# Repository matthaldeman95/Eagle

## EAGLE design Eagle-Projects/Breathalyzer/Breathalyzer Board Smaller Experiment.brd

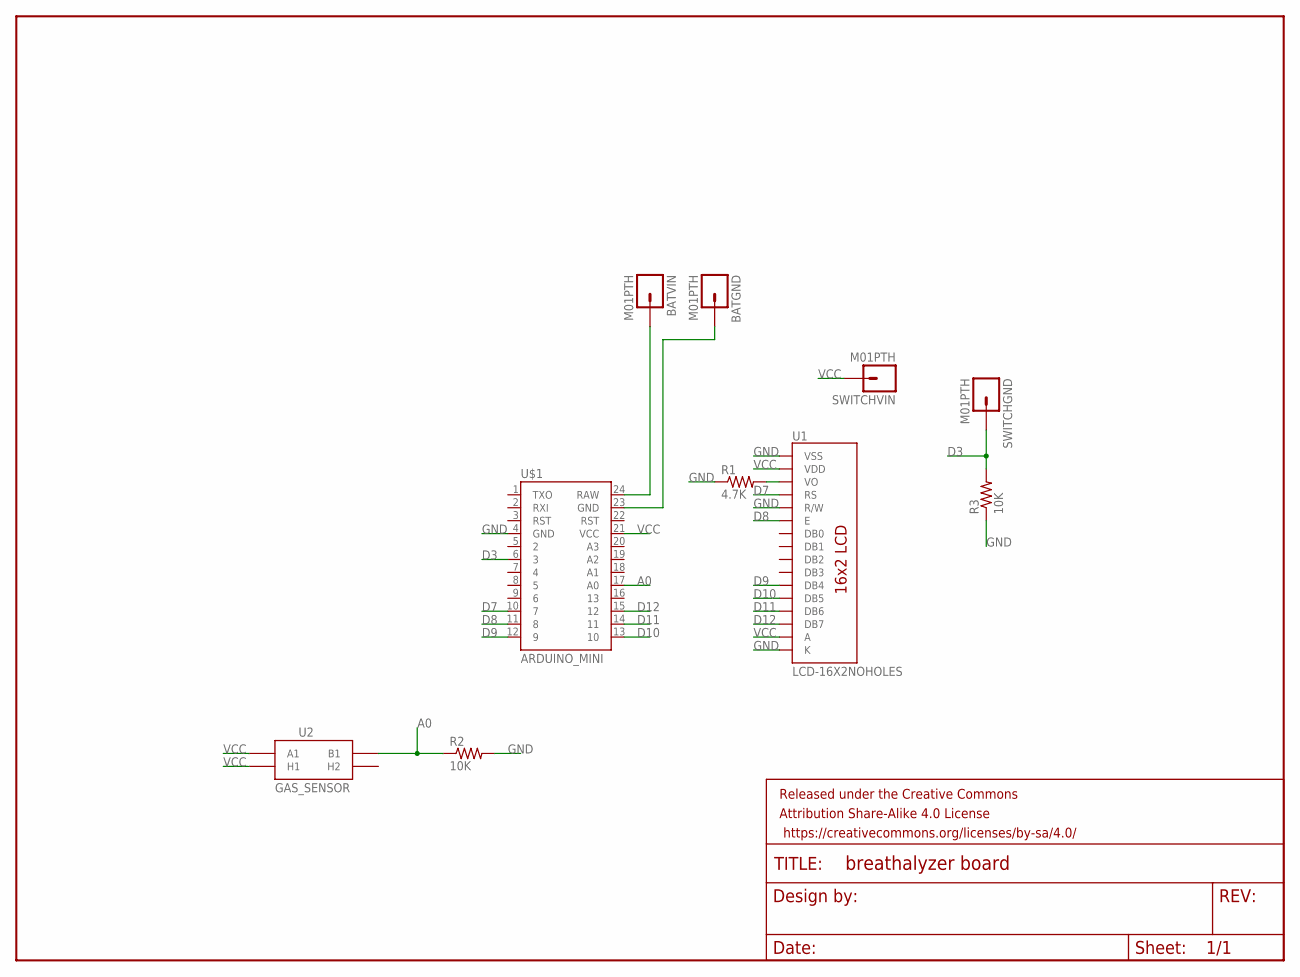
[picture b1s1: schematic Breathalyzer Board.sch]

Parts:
BATGND: M01PTH; 1X01
BATVIN: M01PTH; 1X01
FRAME1: FRAME-LETTER; CREATIVE_COMMONS
R1: 4.7K; AXIAL-0.3
R2, R3: 10K; AXIAL-0.3
SWITCHGND: M01PTH; 1X01
SWITCHVIN: M01PTH; 1X01
U1: LCD-16X2NOHOLES; LCD-16X2_NOHOLES
U2: GAS_SENSOR; MQ-3
U$1: ARDUINO_MINI

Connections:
A0: R2.P$1 (1), U2.B1, U$1.17 (A0)
D3: R3.P$2 (2), SWITCHGND.1, U$1.6 (3)
D7: U1.4 (RS), U$1.10 (7)
D8: U1.6 (E), U$1.11 (8)
D9: U1.11 (DB4), U$1.12 (9)
D10: U1.12 (DB5), U$1.13 (10)
D11: U1.13 (DB6), U$1.14 (11)
D12: U1.14 (DB7), U$1.15 (12)
GND: R1.P$1 (1), R2.P$2 (2), R3.P$1 (1), U1.1 (VSS), U1.5 (R/W), U1.16 (K), U$1.4 (GND)
unnamed: BATVIN.1, U$1.24 (RAW)
unnamed: BATGND.1, U$1.23 (GND)
unnamed: R1.P$2 (2), U1.3 (VO)
VCC: SWITCHVIN.1, U1.2 (VDD), U1.15 (A), U2.A1, U2.HA (H1), U$1.21 (VCC)

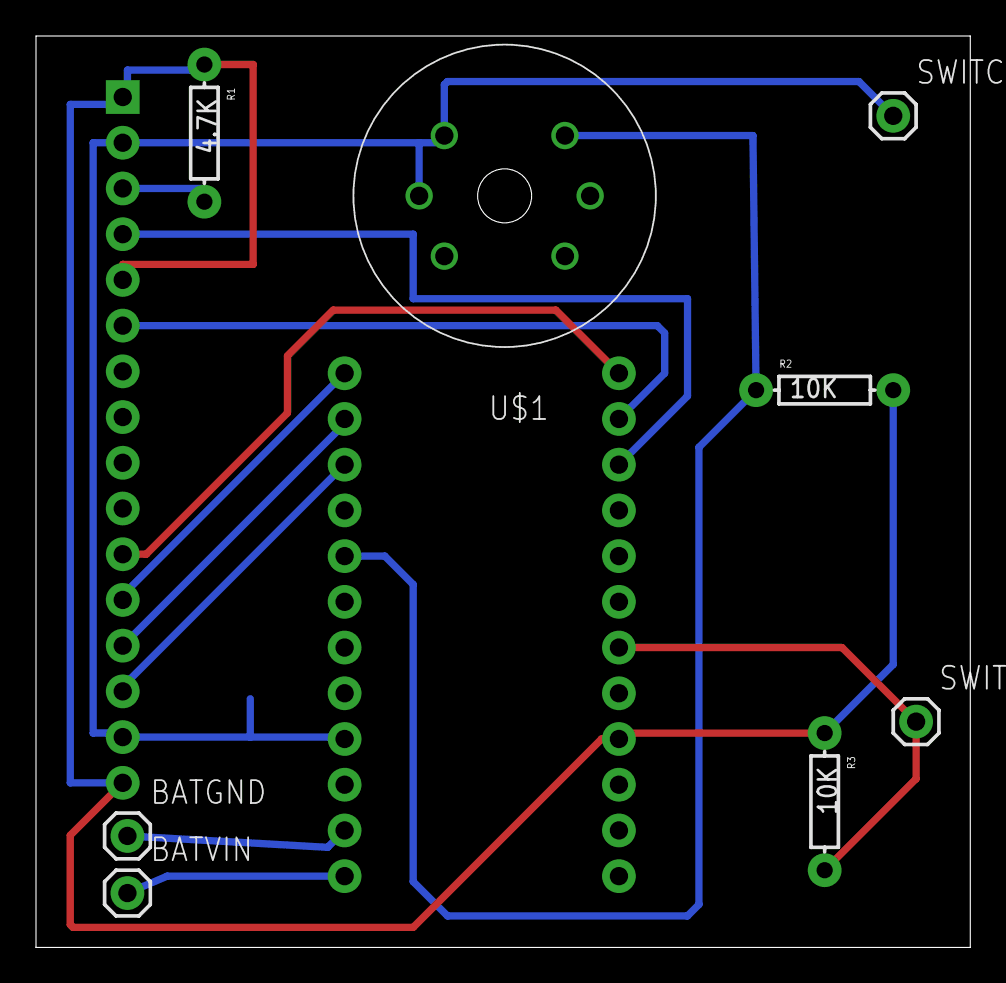
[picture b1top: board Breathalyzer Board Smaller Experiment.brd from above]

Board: 2 copper layers, 51.9 x 50.6 mm, 11 parts (1 on the bottom side), 13 nets.

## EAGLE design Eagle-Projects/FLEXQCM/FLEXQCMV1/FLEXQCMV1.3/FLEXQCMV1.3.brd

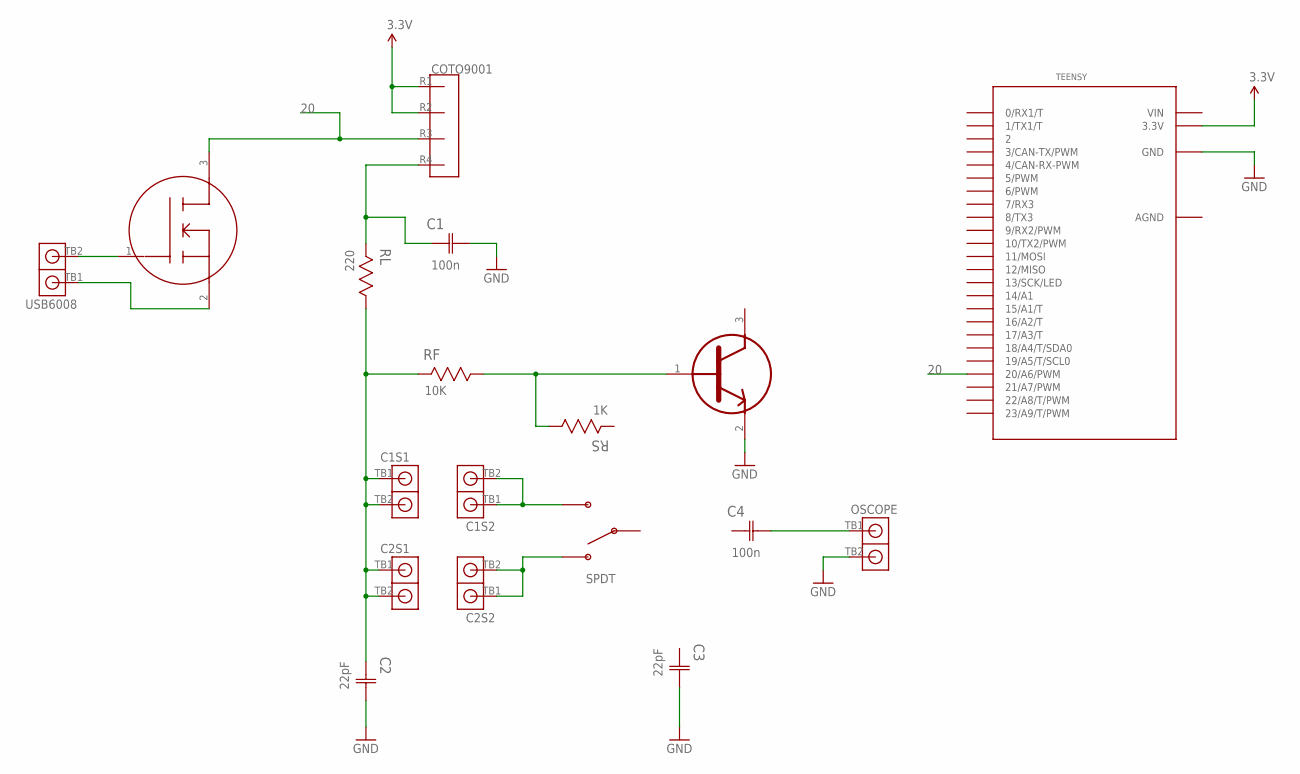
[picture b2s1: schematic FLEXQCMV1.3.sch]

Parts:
C1, C4: 100n; CAPC3216X88N
C1S1, C1S2, C2S1, C2S2: TERMBLOCKX2
C2, C3: 22pF; CAPC3216X88N
COTO9001: COTO9001
OSCOPE: TERMBLOCKX2
RF: 10K; RESC3216X71N
RL: 220; RESC3216X71N
RS: 1K; RESC3216X71N
SPDT: SPDTSWITCH
TEENSY: TEENSY_3.1_DIL; TEENSY3-DIL
U1: FET; SOT95P230X110-3N
U2: BJT; SOT95P230X110-3N
USB6008: TERMBLOCKX2

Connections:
3.3V: COTO9001.R1, COTO9001.R2, TEENSY.3.3V
13: C1S1.TB1, C1S1.TB2, C2.1 (C1), C2S1.TB1, C2S1.TB2, RF.2, RL.1, TEENSY.13 (13/SCK/LED), U2.3 (C)
20: COTO9001.R3, TEENSY.20/A6 (20/A6/PWM), U1.3 (D)
AGND: TEENSY.AGND
GND: C1.2 (C2), C2.2 (C2), C3.2 (C2), OSCOPE.TB2, TEENSY.GND, U2.2 (E)
unnamed: U1.1 (G), USB6008.TB2
unnamed: U1.2 (S), USB6008.TB1
unnamed: C1.1 (C1), COTO9001.R4, RL.2
unnamed: C1S2.TB1, C1S2.TB2, SPDT.SW3
unnamed: RF.1, RS.1, U2.1 (B)
unnamed: C2S2.TB1, C2S2.TB2, SPDT.SW1
unnamed: C3.1 (C1), C4.1 (C1), RS.2, SPDT.SW2
unnamed: C4.2 (C2), OSCOPE.TB1
VIN: TEENSY.VIN

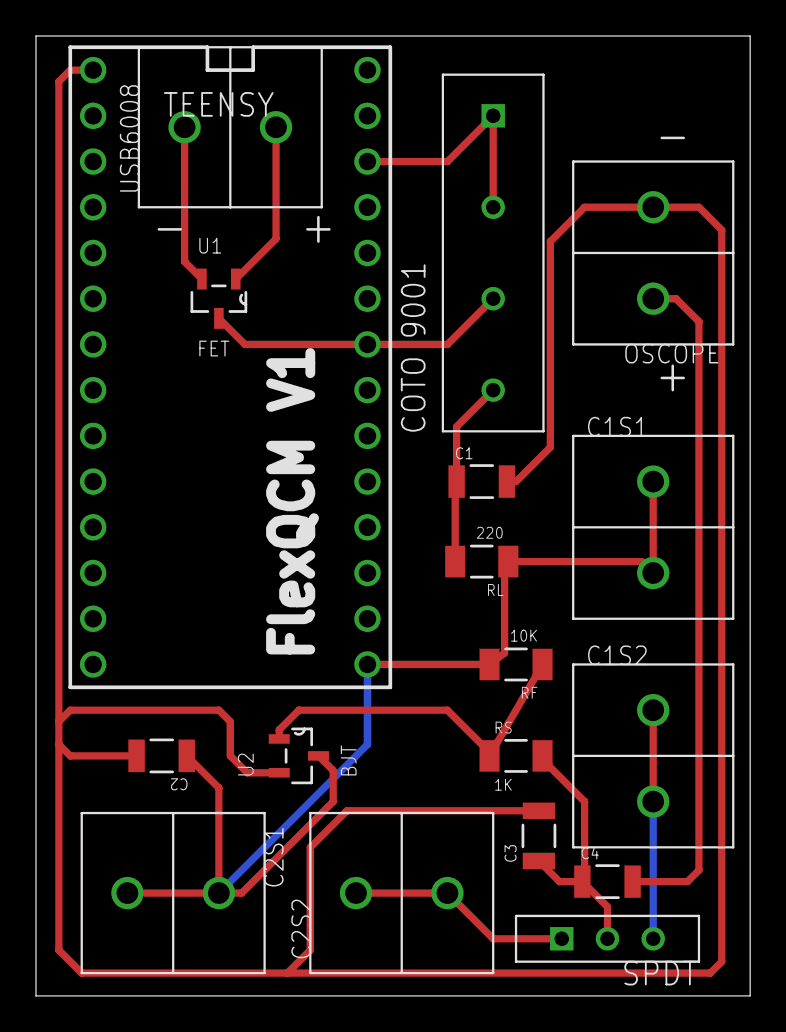
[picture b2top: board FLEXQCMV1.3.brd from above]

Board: 2 copper layers, 39.7 x 53.3 mm, 19 parts (0 on the bottom side), 12 nets.

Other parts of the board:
U$1: ORNLLOGOV6

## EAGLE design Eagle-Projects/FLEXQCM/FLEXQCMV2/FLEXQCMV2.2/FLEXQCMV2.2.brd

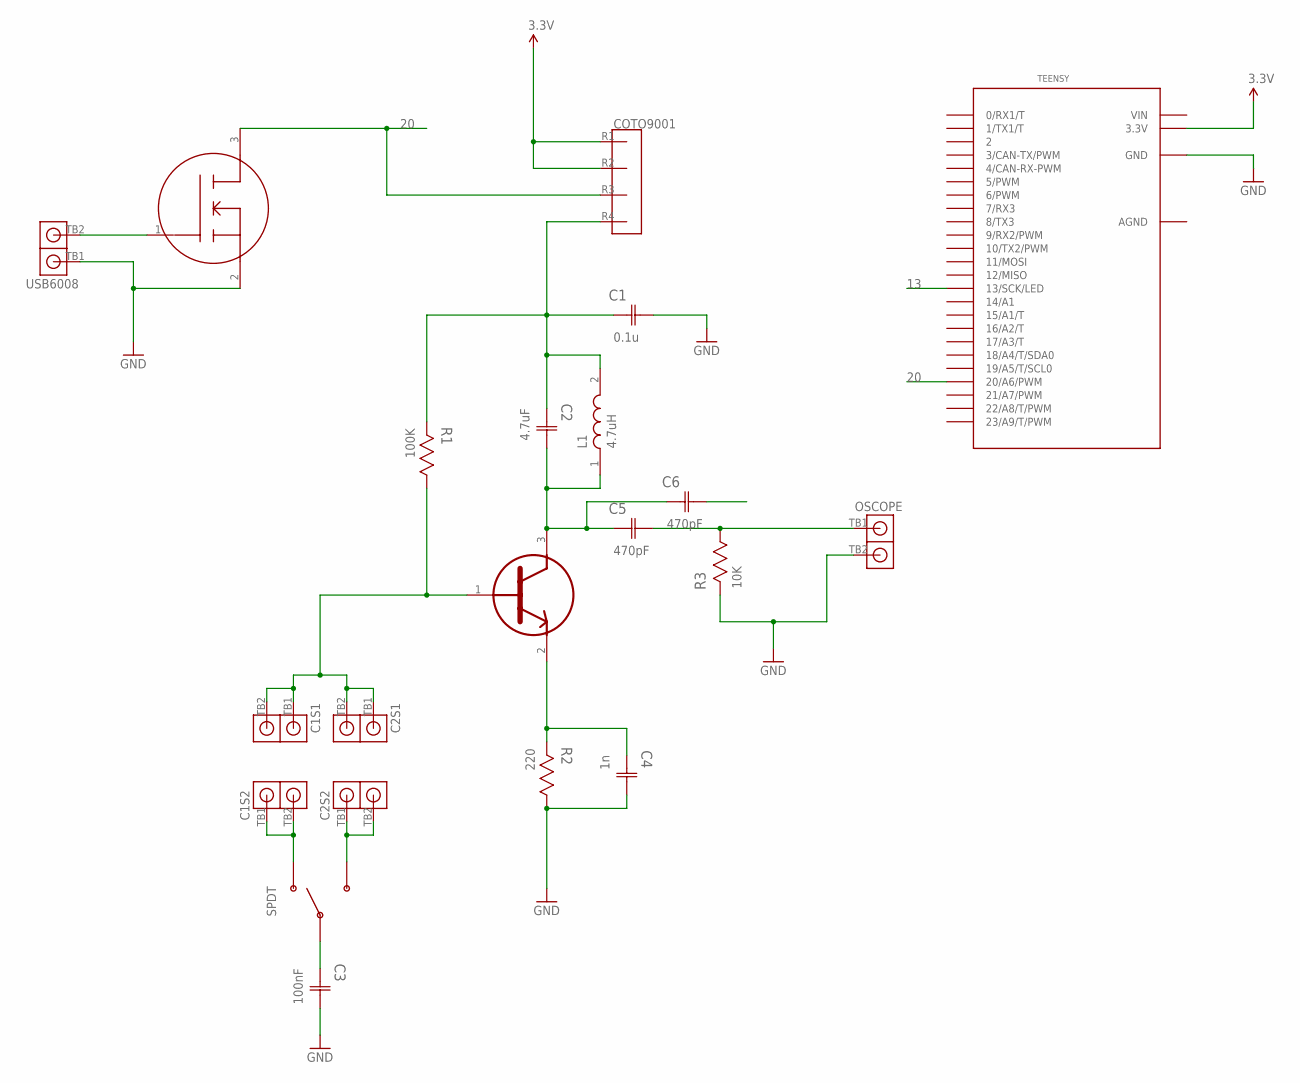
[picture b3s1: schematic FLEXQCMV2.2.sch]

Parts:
C1: 0.1u; CAPC3216X88N
C1S1, C1S2, C2S1, C2S2: TERMBLOCKX2
C2: 4.7uF; CAPC3216X180N
C3: 100nF; CAPC3216X88N
C4: 1n; CAPC3216X88N
C5, C6: 470pF; CAPC3216X100N
COTO9001: COTO9001
L1: 4.7uH; INDC3225X210N
OSCOPE: TERMBLOCKX2
R1: 100K; RESC3216X71N
R2: 220; RESC3216X71N
R3: 10K; RESC3216X71N
SPDT: SPDTSWITCH
TEENSY: TEENSY_3.1_DIL; TEENSY3-DIL
U1: FET; SOT95P230X110-3N
U2: BJT; SOT95P230X110-3N
USB6008: TERMBLOCKX2

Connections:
3.3V: COTO9001.R1, COTO9001.R2, TEENSY.3.3V
13: C6.2 (C2), TEENSY.13 (13/SCK/LED)
20: COTO9001.R3, TEENSY.20/A6 (20/A6/PWM), U1.3 (D)
AGND: TEENSY.AGND
GND: C1.2 (C2), C3.2 (C2), C4.2 (C2), OSCOPE.TB2, R2.1, R3.2, TEENSY.GND, U1.2 (S), USB6008.TB1
unnamed: U1.1 (G), USB6008.TB2
unnamed: C4.1 (C1), R2.2, U2.2 (E)
unnamed: C1S2.TB1, C1S2.TB2, SPDT.SW1
unnamed: C1.1 (C1), C2.1 (C1), COTO9001.R4, L1.2, R1.2
unnamed: C1S1.TB1, C1S1.TB2, C2S1.TB1, C2S1.TB2, R1.1, U2.1 (B)
unnamed: C3.1 (C1), SPDT.SW2
unnamed: C2S2.TB1, C2S2.TB2, SPDT.SW3
unnamed: C2.2 (C2), C5.1 (C1), C6.1 (C1), L1.1, U2.3 (C)
unnamed: C5.2 (C2), OSCOPE.TB1, R3.1
VIN: TEENSY.VIN

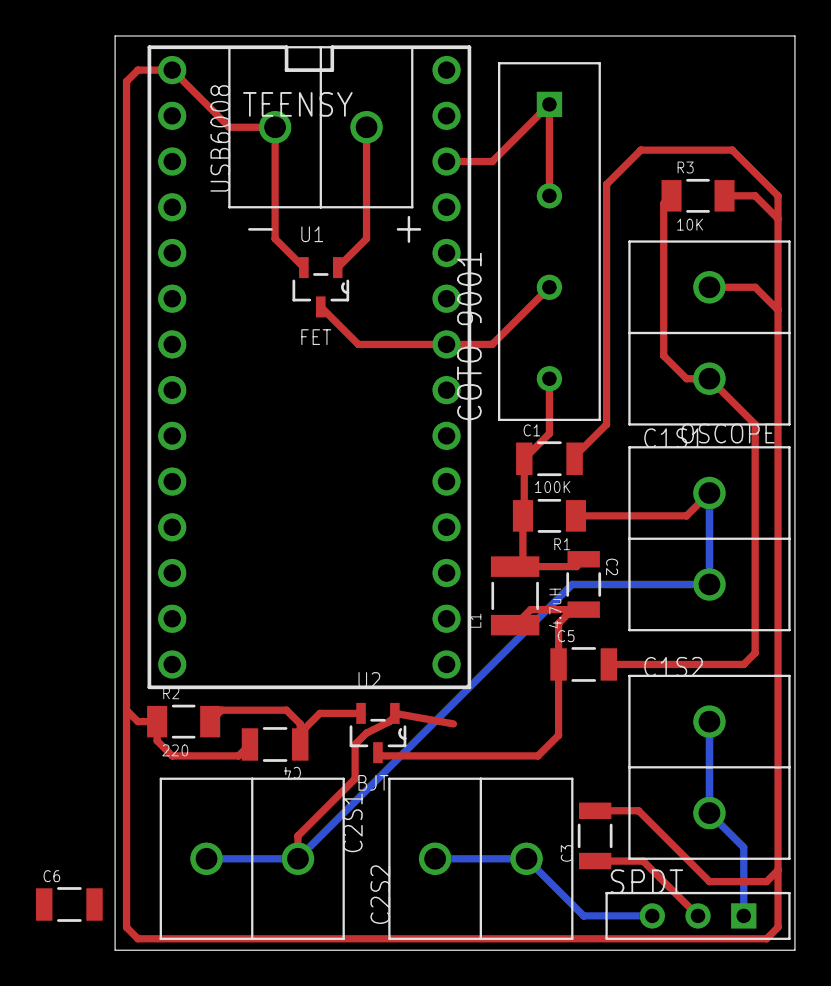
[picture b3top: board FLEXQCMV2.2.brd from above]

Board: 2 copper layers, 37.8 x 50.8 mm, 21 parts (0 on the bottom side), 13 nets.

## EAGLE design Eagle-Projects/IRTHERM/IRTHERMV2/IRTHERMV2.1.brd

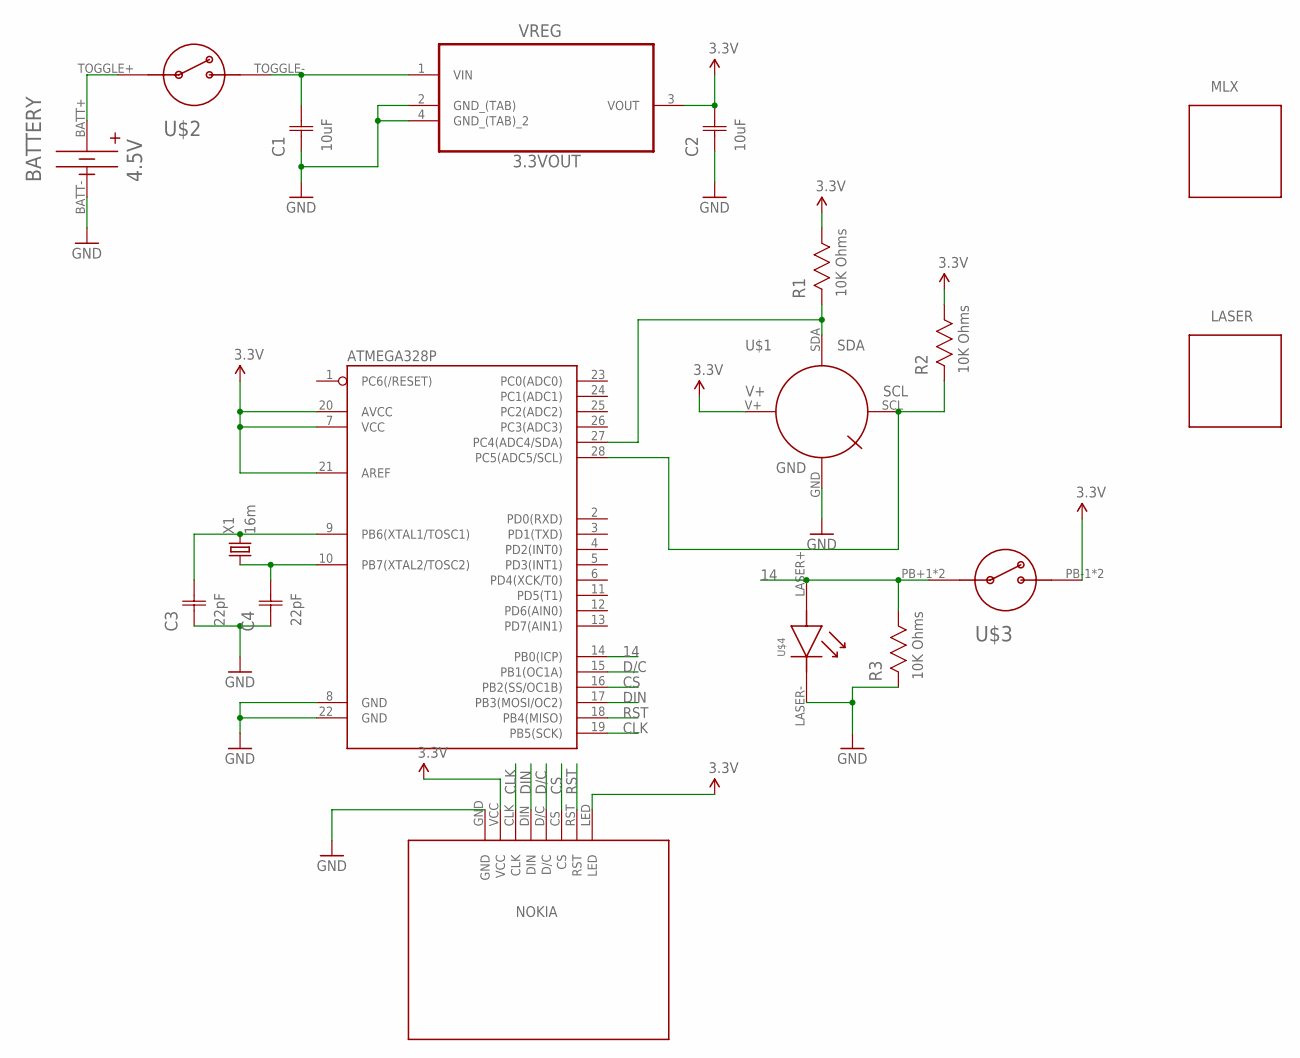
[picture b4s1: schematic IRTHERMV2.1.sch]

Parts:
ATMEGA328P: ATMEGA328P_PDIP; DIL28-3
BATTERY: 4.5V; KEYSTONE2479
C1, C2: 10uF; CAPC3216X180N
C3, C4: 22pF; CAPC3216X88N
LASER: KEYSTONECLIP; KEYSTONE50
MLX: KEYSTONECLIP; KEYSTONE50
R1, R2, R3: 10K Ohms; RESC3216X71N
U$1: MLX90614
U$2: 1683ON-OFFTOGGLE
U$3: 1009PUSHBUTTON
U$4: LASER
U$5: NOKIA
VREG: 3.3VOUT; SOT230P700X180-4N
X1: 16m; HC49US

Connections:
3.3V: ATMEGA328P.7 (VCC), ATMEGA328P.20 (AVCC), ATMEGA328P.21 (AREF), C2.2 (C2), R1.1, R2.1, U$1.V+ (MLXV+), U$3.PB-1 (ONOFF-), U$3.PB-2 (ONOFF-), U$5.LED, U$5.VCC, VREG.3 (VOUT)
14: ATMEGA328P.14 (PB0(ICP)), R3.1, U$3.PB+1 (ONOFF+), U$3.PB+2 (ONOFF+), U$4.LASER+
CLK: ATMEGA328P.19 (PB5(SCK)), U$5.CLK
CS: ATMEGA328P.16 (PB2(SS/OC1B)), U$5.CS
D/C: ATMEGA328P.15 (PB1(OC1A)), U$5.D/C
DIN: ATMEGA328P.17 (PB3(MOSI/OC2)), U$5.DIN
GND: ATMEGA328P.8 (GND), ATMEGA328P.22 (GND), BATTERY.BATT-, C1.1 (C1), C2.1 (C1), C3.1 (C1), C4.1 (C1), R3.2, U$1.GND (MLXGND), U$4.LASER- (LASERGND), U$5.GND, VREG.2 (GND_(TAB)), VREG.4 (GND_(TAB)_2)
unnamed: BATTERY.BATT+, U$2.TOGGLE+ (ONOFF+)
unnamed: C1.2 (C2), U$2.TOGGLE- (ONOFF-), VREG.1 (VIN)
unnamed: ATMEGA328P.27 (PC4(ADC4/SDA)), R1.2, U$1.SDA (MLXSDA)
unnamed: ATMEGA328P.28 (PC5(ADC5/SCL)), R2.2, U$1.SCL (MLXSCL)
unnamed: ATMEGA328P.9 (PB6(XTAL1/TOSC1)), C3.2 (C2), X1.2
unnamed: ATMEGA328P.10 (PB7(XTAL2/TOSC2)), C4.2 (C2), X1.1
RST: ATMEGA328P.18 (PB4(MISO)), U$5.RST

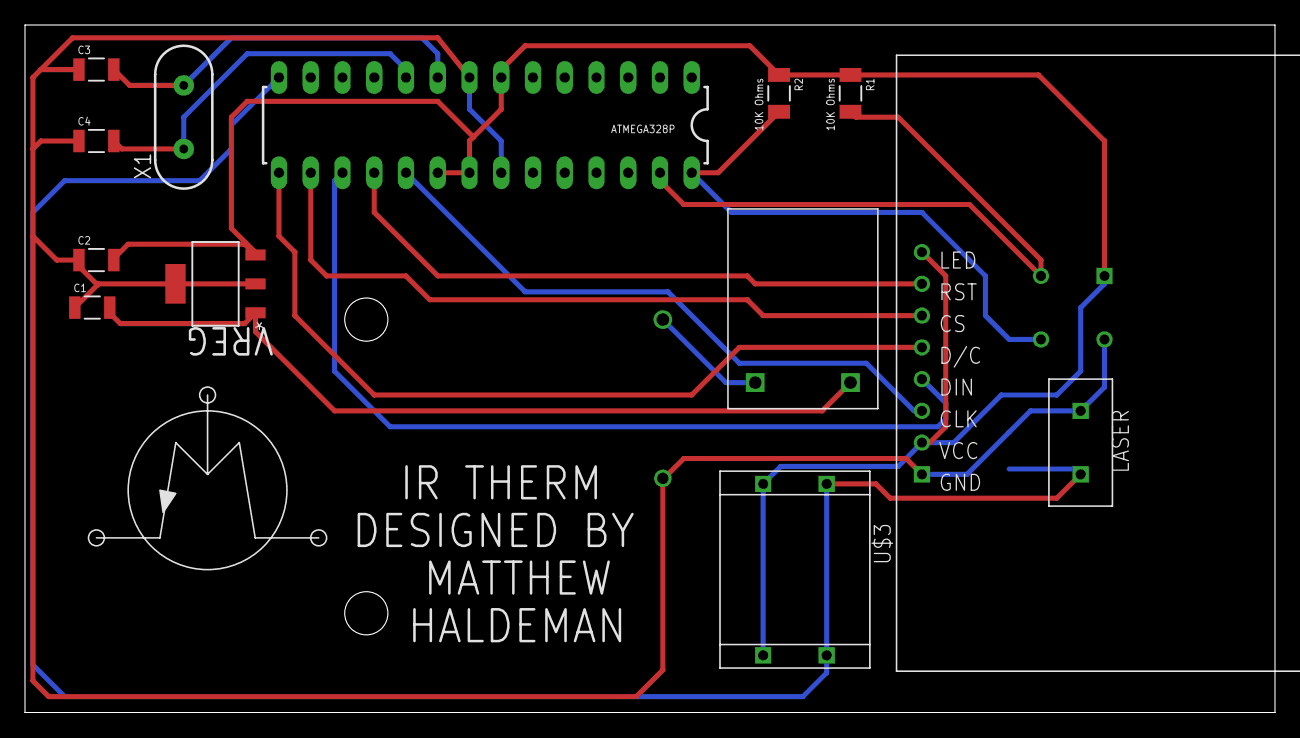
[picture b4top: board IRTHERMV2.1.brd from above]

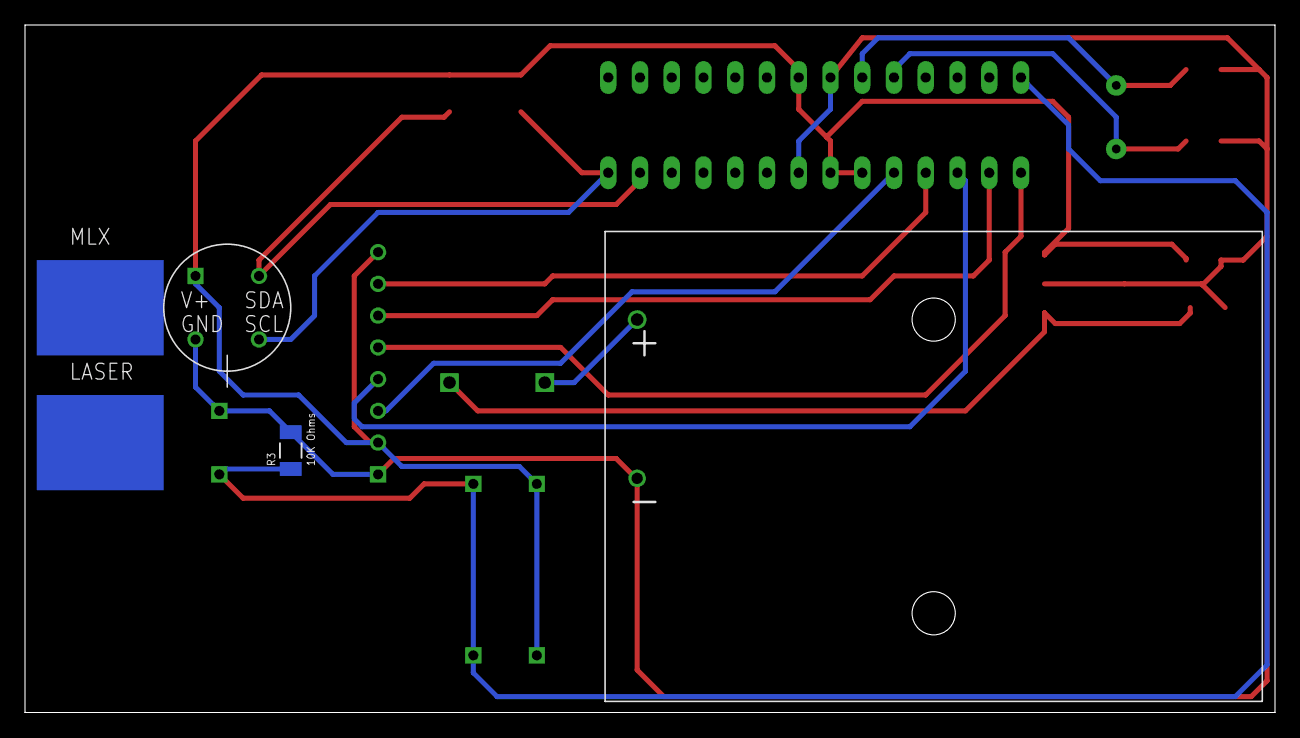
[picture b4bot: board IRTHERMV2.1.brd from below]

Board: 2 copper layers, 100.0 x 55.0 mm, 19 parts (5 on the bottom side), 14 nets.

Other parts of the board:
U$6: SYMBOL

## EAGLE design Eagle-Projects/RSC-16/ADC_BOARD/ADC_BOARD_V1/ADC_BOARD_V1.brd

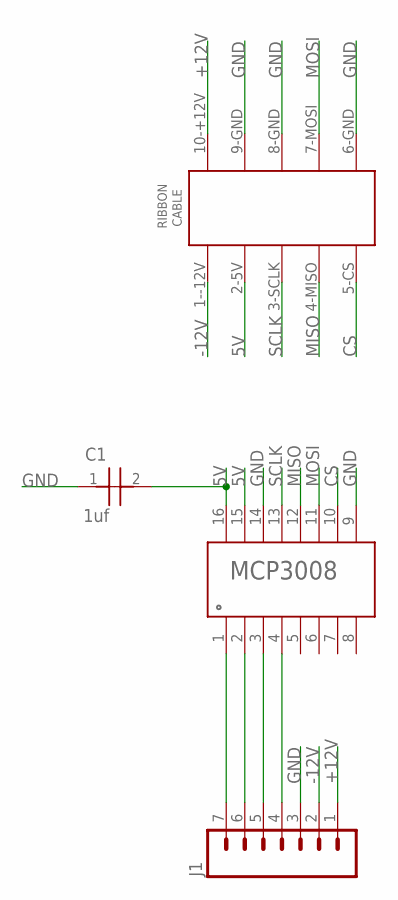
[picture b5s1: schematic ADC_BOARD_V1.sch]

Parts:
C1: 1uf; CAP1206
J1: M07; 1X07
U$1: 5X2RIBBONCONNECTOR
U$2: MCP3008-SOIC16; SOIC16N

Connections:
5V: C1.2, U$1.2-5V, U$2.15 (15-VREF), U$2.16 (16-VDD)
+12V: J1.1, U$1.10-+12V
-12V: J1.2, U$1.1--12V
CS: U$1.5-CS, U$2.10 (10-CS)
GND: C1.1, J1.3, U$1.6-GND, U$1.8-GND, U$1.9-GND, U$2.9 (9-DGND), U$2.14 (14-AGND)
MISO: U$1.4-MISO, U$2.12 (12-DOUT)
MOSI: U$1.7-MOSI, U$2.11 (11-DIN)
unnamed: J1.7, U$2.1 (1-CH0)
unnamed: J1.6, U$2.2 (2-CH1)
unnamed: J1.5, U$2.3 (3-CH2)
unnamed: J1.4, U$2.4 (4-CH3)
SCLK: U$1.3-SCLK, U$2.13 (13-CLK)

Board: 2 copper layers, 4 parts (0 on the bottom side), 12 nets, no tracks yet.

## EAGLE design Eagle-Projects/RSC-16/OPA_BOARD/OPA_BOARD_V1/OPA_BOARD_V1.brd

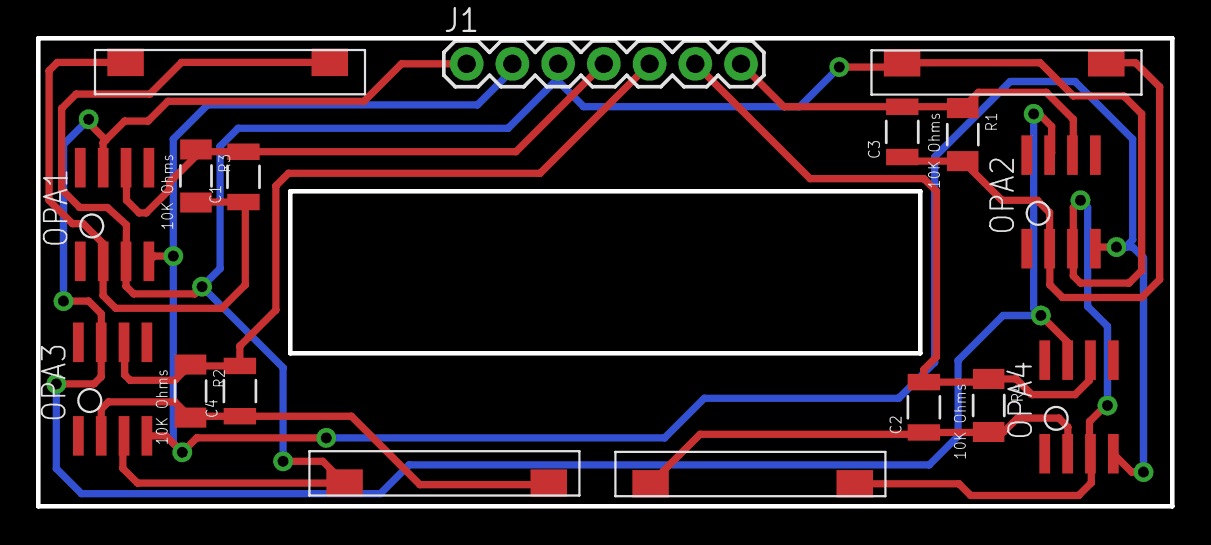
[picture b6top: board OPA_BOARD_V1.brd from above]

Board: 2 copper layers, 63.0 x 26.0 mm, 17 parts (0 on the bottom side), 11 nets.

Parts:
C1, C2, C3, C4: 10nF; CAP1206
J1: 1X07
OPA1, OPA2, OPA3, OPA4: SOIC8
R1, R2, R3, R4: 10K Ohms; RES1206
SP1, SP2, SP3, SP4: PANELPAD; PANELPADS

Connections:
+12V: J1.1, OPA1.7, OPA2.7, OPA3.7, OPA4.7
-12V: J1.2, OPA1.4, OPA2.4, OPA3.4, OPA4.4
CH0: C1.2, J1.4, OPA1.6, R3.1
CH1: C4.2, J1.5, OPA3.6, R2.1
CH2: C2.2, J1.6, OPA4.6, R4.1
CH3: C3.2, J1.7, OPA2.6, R1.1
GND: J1.3, OPA1.3, OPA2.3, OPA3.3, OPA4.3, SP1.P$1, SP2.P$2, SP3.P$1, SP4.P$2
unnamed: C1.1, OPA1.2, R3.2, SP1.P$2
unnamed: C2.1, OPA4.2, R4.2, SP4.P$1
unnamed: C4.1, OPA3.2, R2.2, SP3.P$2
unnamed: C3.1, OPA2.2, R1.2, SP2.P$1

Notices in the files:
parts and their libraries:
SparkFun-Connectors: Licensing: Creative Commons ShareAlike 4.0 International - https://creativecommons.org/licenses/by-sa/4.0
SparkFun-Aesthetics: Released under the Creative Commons Attribution Share-Alike 4.0 License
SparkFun-Aesthetics: https://creativecommons.org/licenses/by-sa/4.0
